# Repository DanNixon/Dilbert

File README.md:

# Dilbert

An interactive badge based on the ESP8266.

For getting started and general information see [GUIDE.md](GUIDE.md).

## Features

- ESP8266
- Colour LCD
- D-pad + A/B buttons
- 8 NeoPixels
- UART, i2c, digital IO and NeoPixel expansion headers

## Links

- Repository: https://github.com/DanNixon/Dilbert
- Travis CI: https://travis-ci.org/DanNixon/Dilbert
- Documentation: http://dannixon.github.io/Dilbert

## Contributing code

Cool stuff to run on the badge is very welcome.

See [CONTRIBUTING.md](CONTRIBUTING.md).

## Requirements

Uses the following Arduino libraries:

- [Adafruit ILI9341](https://github.com/Links2004/Adafruit_ILI9341) (the
  Links2004 fork can provide much faster display updates than the [Adafruit
  library](https://github.com/adafruit/Adafruit_ILI9341))
- [Adafruit GFX](https://github.com/adafruit/Adafruit-GFX-Library)
- [Adafruit NeoPixel](https://github.com/adafruit/Adafruit_NeoPixel)
- [Adafruit MCP23017](https://github.com/adafruit/Adafruit-MCP23017-Arduino-Library)
  (modified version included in this repository)
- [Universal Inputs](https://github.com/DanNixon/ArduinoUniversalInput)

## Parts

- ESP-12
  ([buy](https://www.adafruit.com/product/2491))
- 2.2" TFT display with ILI9341 driver
  ([buy](http://www.ebay.co.uk/itm/262448340175))
- [MCP23017](http://ww1.microchip.com/downloads/en/DeviceDoc/21952b.pdf)
  ([buy](http://www.mouser.co.uk/search/ProductDetail.aspx?R=0virtualkey0virtualkeyMCP23017-E-SO))
- [AP2112](http://www.diodes.com/_files/datasheets/AP2112.pdf)
  ([buy](http://www.digikey.co.uk/product-detail/en/diodes-incorporated/AP2112K-3.3TRG1/AP2112K-3.3TRG1DICT-ND/4505257))
- 8x NeoPixels
  ([buy](https://www.adafruit.com/products/1655))
- 6x switches
  ([buy](http://www.digikey.co.uk/product-detail/en/panasonic-electronic-components/EVQ-PE504K/P13589S-ND/1245482))
- 1uF and 10uF 0805 capacitors
- 1K and 10K 0805 resistors

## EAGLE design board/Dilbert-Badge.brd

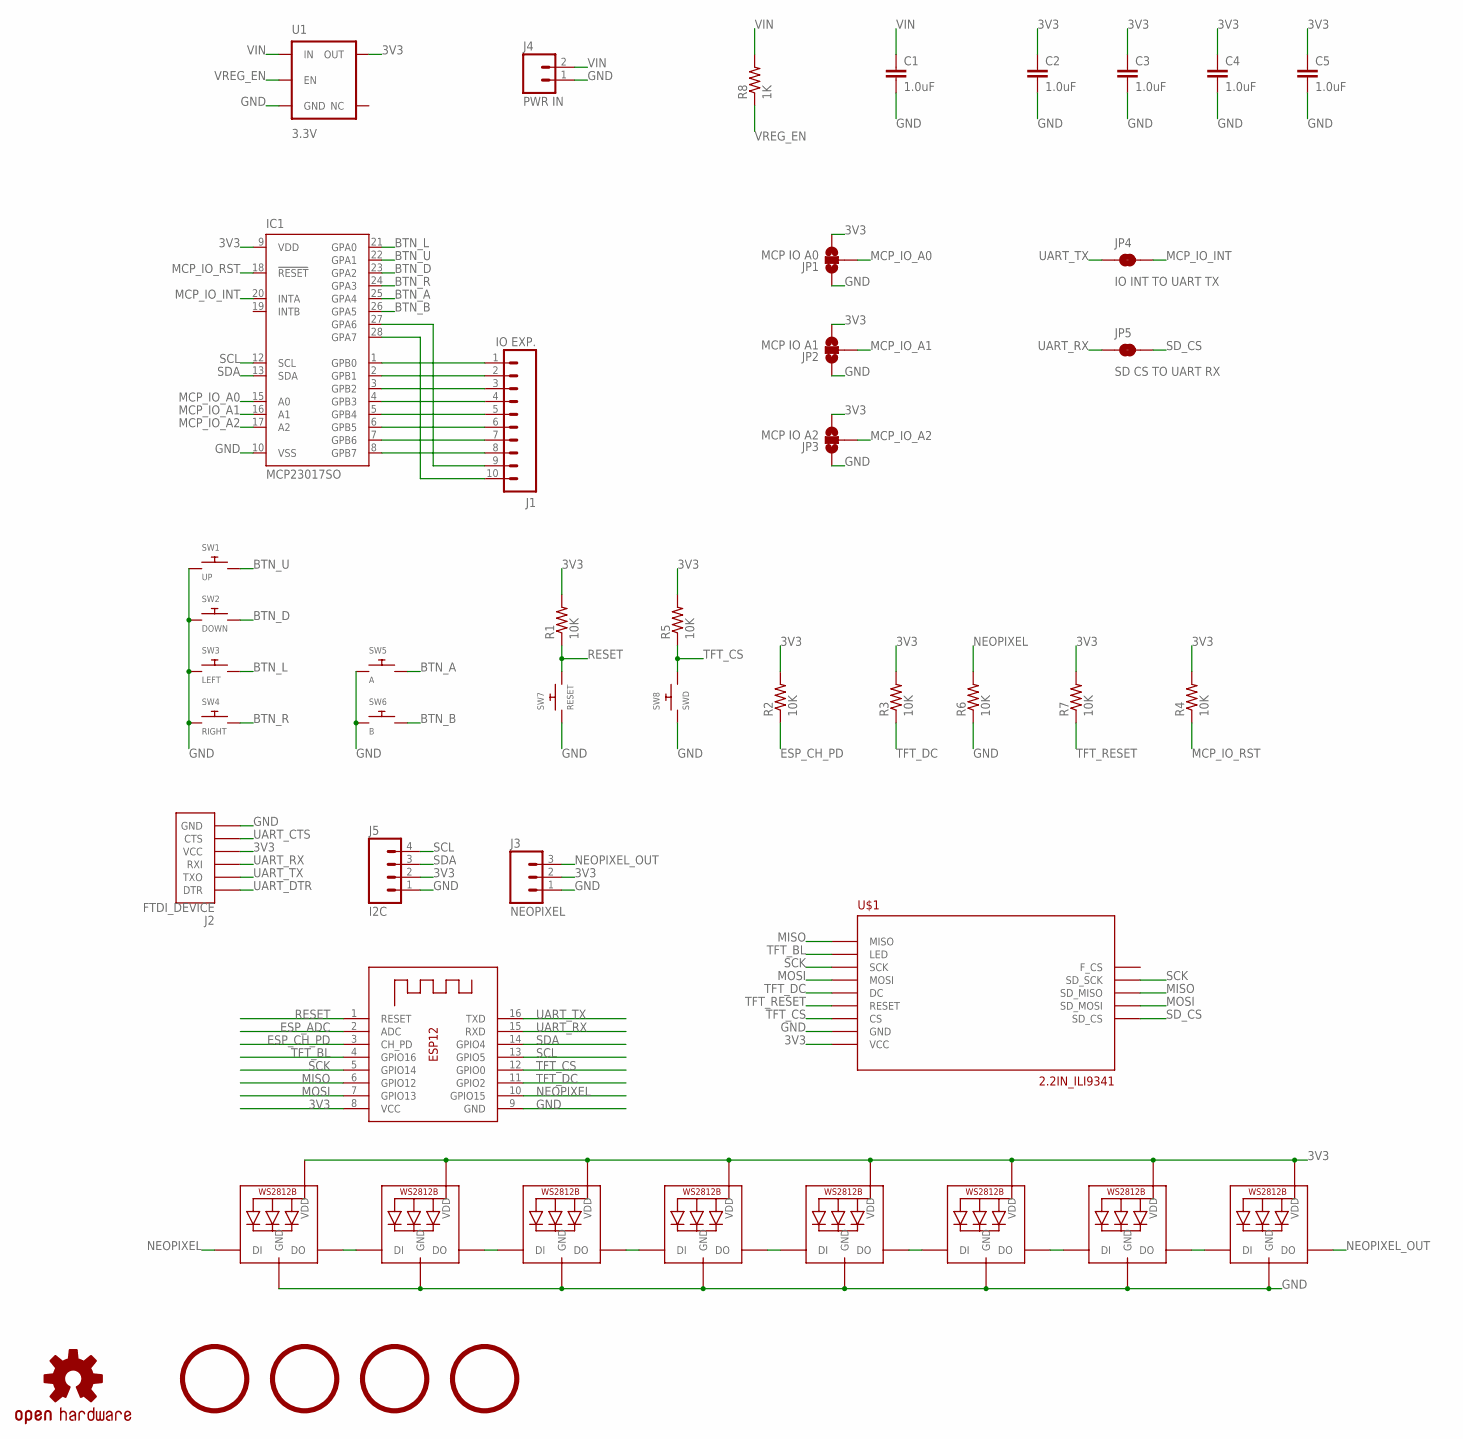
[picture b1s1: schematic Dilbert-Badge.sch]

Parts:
C1, C2, C3, C4, C5: 1.0uF; 0805-CAP
IC1: MCP23017SO; SO28W
J1: IO EXP.; 1X10
J2: FTDI_DEVICE; FTDI_DEVICE_SIDE
J3: NEOPIXEL; 1X03
J4: PWR IN; 1X02
J5: I2C; 1X04
JP1: MCP IO A0; PAD-JUMPER-3-NO_YES_SILK
JP2: MCP IO A1; PAD-JUMPER-3-NO_YES_SILK
JP3: MCP IO A2; PAD-JUMPER-3-NO_YES_SILK
JP4: IO INT TO UART TX; PAD-JUMPER-2-NC_BY_TRACE_NO_SILK
JP5: SD CS TO UART RX; PAD-JUMPER-2-NC_BY_TRACE_NO_SILK
LED1, LED2, LED3, LED4, LED5, LED6, LED7, LED8: WS2812B5050; WS2812B
LOGO1: OSHW-LOGOL; OSHW-LOGO-L
R1, R2, R3, R4, R5, R6, R7: 10K; R0805
R8: 1K; R0805
SW1: UP; TACT_PANA-EVQ
SW2: DOWN; TACT_PANA-EVQ
SW3: LEFT; TACT_PANA-EVQ
SW4: RIGHT; TACT_PANA-EVQ
SW5: A; TACT_PANA-EVQ
SW6: B; TACT_PANA-EVQ
SW7: RESET; TACT_PANA-EVQ
SW8: SWD; TACT_PANA-EVQ
U1: 3.3V; SOT23-5
U$1: 2.2IN_ILI9341
U$2, U$3, U$4, U$5: 5MM_MOUNTING_HOLE; 5MM_HOLE
X1: ESP-12

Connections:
3V3: C2.1, C3.1, C4.1, C5.1, IC1.9 (VDD), J2.P$4 (VCC), J3.2, J5.2, JP1.3, JP2.3, JP3.3, LED1.1-VDD (VDD), LED2.1-VDD (VDD), LED3.1-VDD (VDD), LED4.1-VDD (VDD), LED5.1-VDD (VDD), LED6.1-VDD (VDD), LED7.1-VDD (VDD), LED8.1-VDD (VDD), R1.2, R2.2, R3.2, R4.2, R5.2, R7.2, U1.5 (OUT), U$1.VCC, X1.8 (VCC)
BTN_A: IC1.25 (GPA4), SW5.P$2
BTN_B: IC1.26 (GPA5), SW6.P$2
BTN_D: IC1.23 (GPA2), SW2.P$2
BTN_L: IC1.21 (GPA0), SW3.P$2
BTN_R: IC1.24 (GPA3), SW4.P$2
BTN_U: IC1.22 (GPA1), SW1.P$2
ESP_ADC: X1.2 (ADC)
ESP_CH_PD: R2.1, X1.3 (CH_PD)
GND: C1.2, C2.2, C3.2, C4.2, C5.2, IC1.10 (VSS), J2.P$6 (GND), J3.1, J4.1, J5.1, JP1.1, JP2.1, JP3.1, LED1.3-GND (GND), LED2.3-GND (GND), LED3.3-GND (GND), LED4.3-GND (GND), LED5.3-GND (GND), LED6.3-GND (GND), LED7.3-GND (GND), LED8.3-GND (GND), R6.1, SW1.P$1, SW2.P$1, SW3.P$1, SW4.P$1, SW5.P$1, SW6.P$1, SW7.P$1, SW8.P$1, U1.2 (GND), U$1.GND, X1.9 (GND)
MCP_IO_A0: IC1.15 (A0), JP1.2
MCP_IO_A1: IC1.16 (A1), JP2.2
MCP_IO_A2: IC1.17 (A2), JP3.2
MCP_IO_INT: IC1.20 (INTA), JP4.2
MCP_IO_RST: IC1.18 (!RESET), R4.1
MISO: U$1.MISO, U$1.SD_MISO, X1.6 (GPIO12)
MOSI: U$1.MOSI, U$1.SD_MOSI, X1.7 (GPIO13)
unnamed: LED1.2-DOUT (DO), LED2.4-DIN (DI)
unnamed: IC1.1 (GPB0), J1.1
unnamed: IC1.2 (GPB1), J1.2
unnamed: IC1.3 (GPB2), J1.3
unnamed: IC1.4 (GPB3), J1.4
unnamed: IC1.28 (GPA7), J1.10
unnamed: IC1.27 (GPA6), J1.9
unnamed: IC1.8 (GPB7), J1.8
unnamed: IC1.7 (GPB6), J1.7
unnamed: IC1.6 (GPB5), J1.6
unnamed: IC1.5 (GPB4), J1.5
unnamed: LED2.2-DOUT (DO), LED3.4-DIN (DI)
unnamed: LED3.2-DOUT (DO), LED4.4-DIN (DI)
unnamed: LED4.2-DOUT (DO), LED5.4-DIN (DI)
unnamed: LED5.2-DOUT (DO), LED6.4-DIN (DI)
unnamed: LED6.2-DOUT (DO), LED7.4-DIN (DI)
unnamed: LED7.2-DOUT (DO), LED8.4-DIN (DI)
NEOPIXEL: LED1.4-DIN (DI), R6.2, X1.10 (GPIO15)
NEOPIXEL_OUT: J3.3, LED8.2-DOUT (DO)
RESET: R1.1, SW7.P$2, X1.1 (RESET)
SCK: U$1.SCK, U$1.SD_SCK, X1.5 (GPIO14)
SCL: IC1.12 (SCL), J5.4, X1.13 (GPIO5)
SDA: IC1.13 (SDA), J5.3, X1.14 (GPIO4)
SD_CS: JP5.2, U$1.SD_CS
TFT_BL: U$1.LED, X1.4 (GPIO16)
TFT_CS: R5.1, SW8.P$2, U$1.CS, X1.12 (GPIO0)
TFT_DC: R3.1, U$1.DC, X1.11 (GPIO2)
TFT_RESET: R7.1, U$1.RESET
UART_CTS: J2.P$5 (CTS)
UART_DTR: J2.P$1 (DTR)
UART_RX: J2.P$3 (RXI), JP5.1, X1.15 (RXD)
UART_TX: J2.P$2 (TXO), JP4.1, X1.16 (TXD)
VIN: C1.1, J4.2, R8.2, U1.1 (IN)
VREG_EN: R8.1, U1.3 (EN)

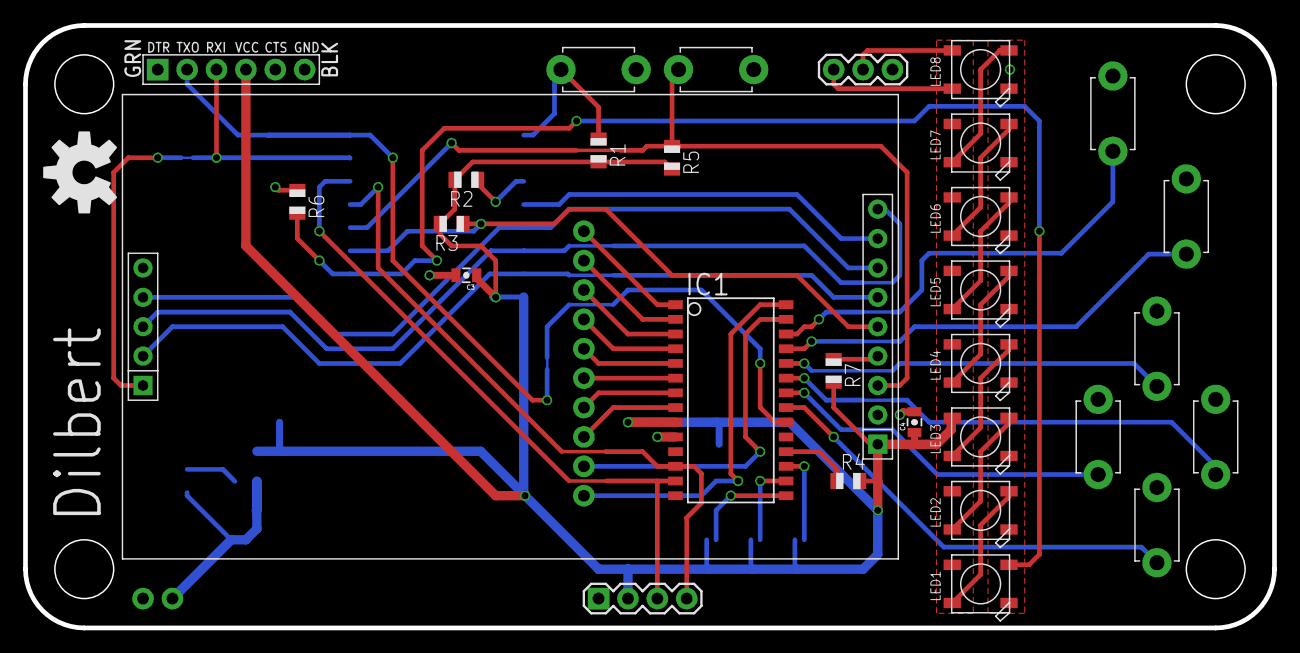
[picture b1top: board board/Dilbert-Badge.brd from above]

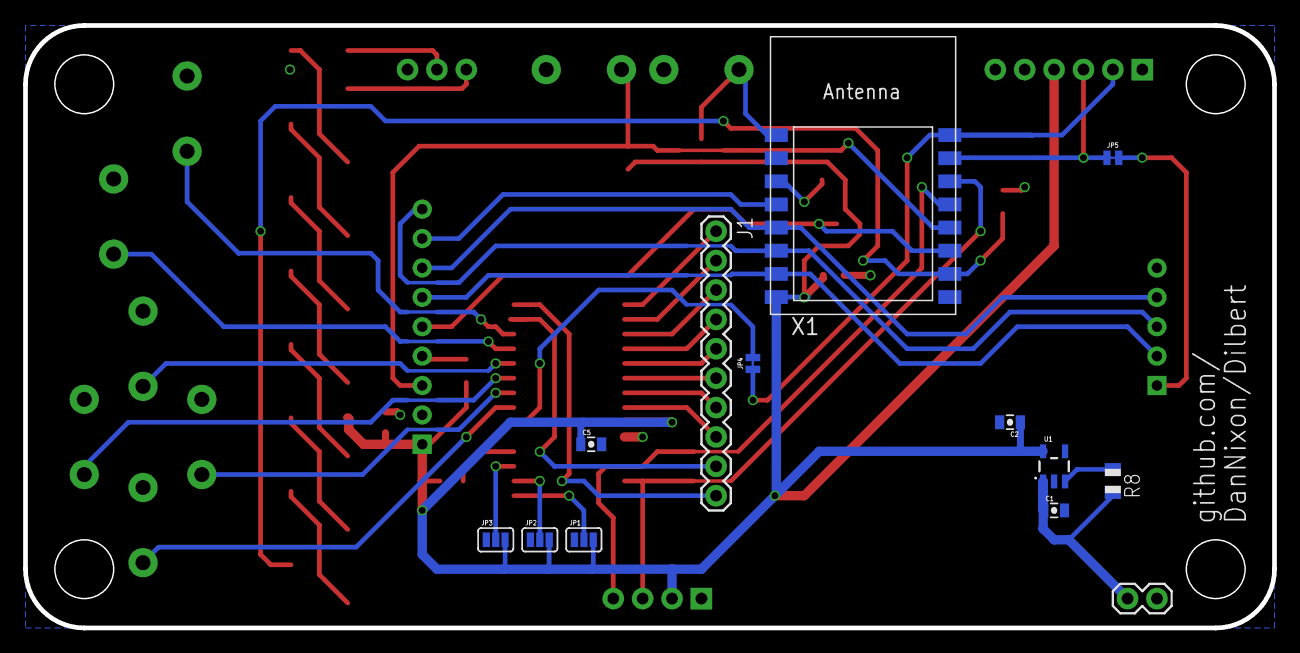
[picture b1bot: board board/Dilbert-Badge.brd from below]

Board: 2 copper layers, 108.0 x 52.1 mm, 48 parts (13 on the bottom side), 48 nets.

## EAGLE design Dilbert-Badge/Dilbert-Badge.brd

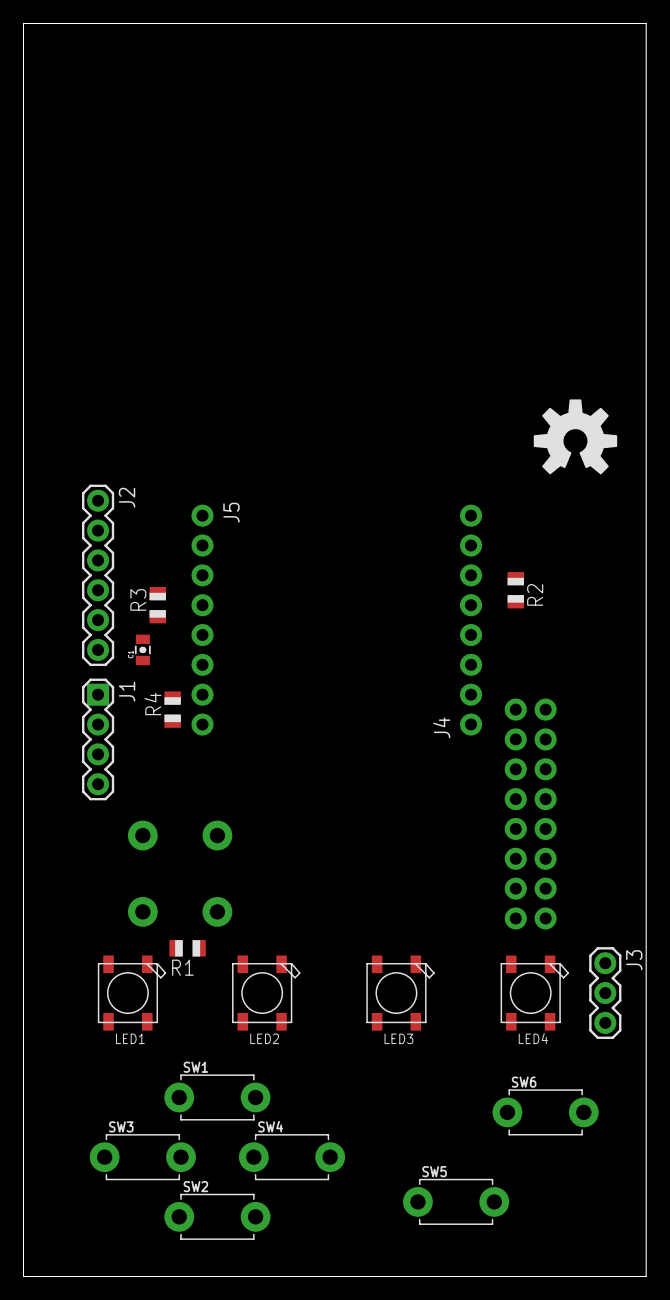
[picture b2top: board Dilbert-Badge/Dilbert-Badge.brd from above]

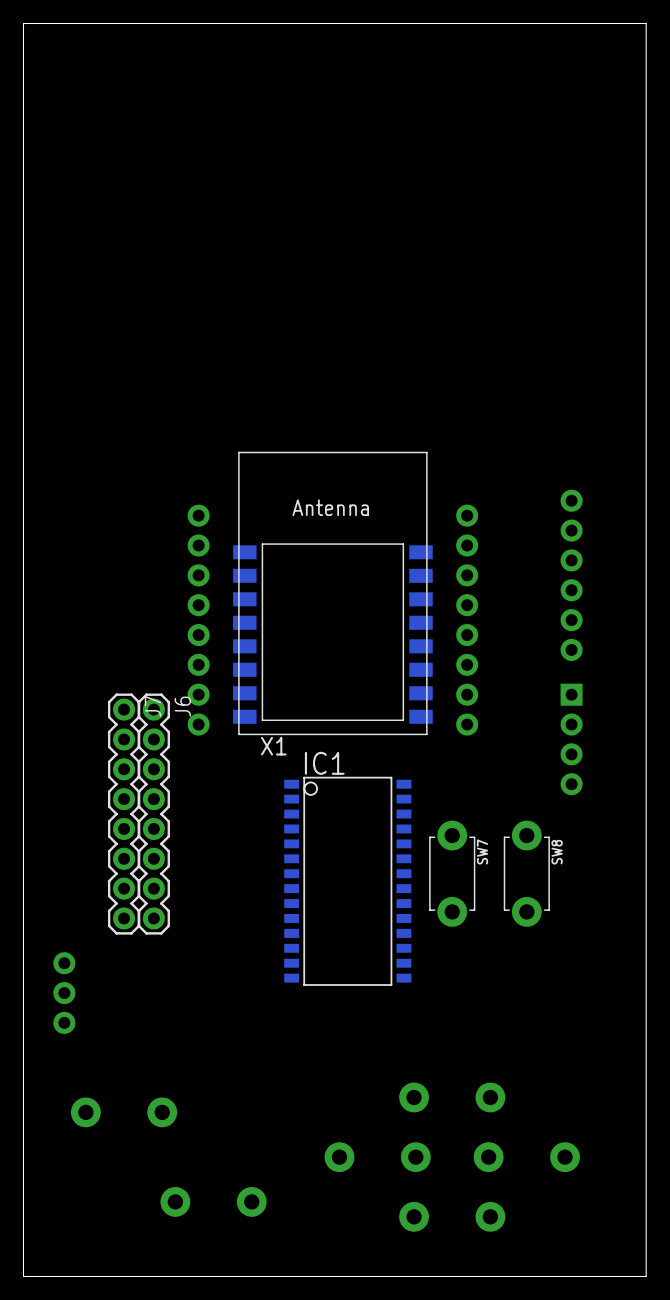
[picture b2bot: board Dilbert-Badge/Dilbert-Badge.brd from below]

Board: 2 copper layers, 53.0 x 106.7 mm, 27 parts (6 on the bottom side), 36 nets, no tracks yet.

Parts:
C1: 0805-CAP
IC1: MCP23017SO; SO28W
J1: I2C; 1X04
J2: UART; 1X06
J3: 1X03
J4, J5: 1X08_NO_SILK
J6: IO_B; 1X08_ROUND
J7: IO_A; 1X08_ROUND
LED1, LED2, LED3, LED4: WS2812B5050; WS2812B
LOGO1: OSHW-LOGOL; OSHW-LOGO-L
R1, R2, R3: 10K; R0805
R4: R0805
SW1: UP; TACT_PANA-EVQ
SW2: DOWN; TACT_PANA-EVQ
SW3: LEFT; TACT_PANA-EVQ
SW4: RIGHT; TACT_PANA-EVQ
SW5: A; TACT_PANA-EVQ
SW6: B; TACT_PANA-EVQ
SW7: RESET; TACT_PANA-EVQ
SW8: SWD; TACT_PANA-EVQ
X1: ESP-12

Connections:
3V3: C1.1, IC1.9, J1.2, J2.4, J3.2, J4.1, LED1.1-VDD, LED2.1-VDD, LED3.1-VDD, LED4.1-VDD, R1.2, R2.2, R3.2, X1.8
BTN_A: IC1.25, J7.5, SW5.P$2
BTN_B: IC1.26, J7.6, SW6.P$2
BTN_D: IC1.22, J7.2, SW2.P$2
BTN_L: IC1.23, J7.3, SW3.P$2
BTN_R: IC1.24, J7.4, SW4.P$2
BTN_U: IC1.21, J7.1, SW1.P$2
ESP_ADC: J4.7, X1.2
ESP_CH_PD: J4.6, R2.1, X1.3
GND: C1.2, IC1.10, J1.1, J2.6, J3.1, J5.8, LED1.3-GND, LED2.3-GND, LED3.3-GND, LED4.3-GND, R4.1, SW1.P$1, SW2.P$1, SW3.P$1, SW4.P$1, SW5.P$1, SW6.P$1, SW7.P$1, SW8.P$1, X1.9
GPIO2: J5.6, R3.1, X1.11
LED_IN: J5.7, LED1.4-DIN, R4.2, X1.10
LED_OUT: J3.3, LED4.2-DOUT
unnamed: LED1.2-DOUT, LED2.4-DIN
unnamed: LED2.2-DOUT, LED3.4-DIN
unnamed: LED3.2-DOUT, LED4.4-DIN
unnamed: J4.5, X1.4
unnamed: J4.4, X1.5
unnamed: J4.2, X1.7
unnamed: J4.3, X1.6
unnamed: J5.3, X1.14
unnamed: IC1.1, J6.1
unnamed: IC1.2, J6.2
unnamed: IC1.8, J6.8
unnamed: IC1.7, J6.7
unnamed: IC1.6, J6.6
unnamed: IC1.5, J6.5
unnamed: IC1.4, J6.4
unnamed: IC1.3, J6.3
unnamed: IC1.28, J7.8
unnamed: IC1.27, J7.7
RESET: J4.8, R1.1, SW7.P$2, X1.1
SCL: IC1.12, J1.4, J5.5, SW8.P$2, X1.12
SDA: IC1.13, J1.3, J5.4, X1.13
UART_RX: J2.3, J5.2, X1.15
UART_TX: J2.2, J5.1, X1.16

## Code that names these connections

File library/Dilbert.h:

/*! @file */

#ifndef _DILBERT_H_
#define _DILBERT_H_

#include <Adafruit_NeoPixel.h>
#include <Adafruit_ILI9341.h>
#include <UniversalInputManager.h>

#include "Adafruit_MCP23017.h"

/**
 * @class Dilbert
 * @author Dan Nixon
 * @brief Main hardware abstraction class.
 */
class Dilbert
{
public:
  static const uint8_t MCP23017_INT_GPIO = 1;   //!< MCP23017 interrupt GPIO (on UART0 Tx)
  static const uint8_t SD_CS_GPIO = 3;          //!< SD chip select GPIO (on UART0 Rx)
  static const uint8_t TFT_CS_GPIO = 0;         //!< TFT chip select GPIO
  static const uint8_t TFT_DC_GPIO = 2;         //!< TFT DC GPIO
  static const uint8_t TFT_BACKLIGHT_GPIO = 16; //!< TFT backlight GPIO
  static const uint8_t NEOPIXEL_GPIO = 15;      //!< NeoPIxel GPIO

  static const uint8_t BUTTON_UP = 1;    //!< Up buppion GPIO (on MCP23017)
  static const uint8_t BUTTON_DOWN = 2;  //!< Down button GPIO (on MCP23017)
  static const uint8_t BUTTON_LEFT = 0;  //!< Left button GPIO (on MCP23017)
  static const uint8_t BUTTON_RIGHT = 3; //!< Right button GPIO (on MCP23017)
  static const uint8_t BUTTON_A = 4;     //!< A button GPIO (on MCP23017)
  static const uint8_t BUTTON_B = 5;     //!< B button GPIO (on MCP23017)

public:
  Dilbert();
  virtual ~Dilbert();

  void begin(size_t numNeoPixels = 8);

  /**
   * @brief Gets the TFT display driver.
   * @returns Reference to display driver
   */
  inline Adafruit_ILI9341 &display()
  {
    return *m_tftDisplay;
  }

  /**
   * @brief Gets the backlight intensity.
   * @return Intensity
   *
   * Where 0 is off and 1023 is brightest.
   */
  uint16_t backlight() const
  {
    return m_backlightIntensity;
  }

  void setBacklightOn(bool on);
  void setBacklight(uint16_t intensity);

  /**
   * @brief Gets the NeoPixel LED driver.
   * @return Reference to NeoPixel driver
   */
  inline Adafruit_NeoPixel &neoPixels()
  {
    return *m_neopixels;
  }

  /**
   * @brief Gets the IO expender driver.
   * @return Reference to the IO expander driver
   *
   * Warning: some of the IO pins are used for specific functions that are
   * managed elsewhere, do not set a pin that alreadyhas a function, this will
   * probably break something else.
   */
  inline Adafruit_MCP23017 &io()
  {
    return *m_io;
  }

  /**
   * @brief Gets the button manager.
   * @return Reference to the button manager
   */
  inline UniversalInputManager &buttons()
  {
    return *m_buttons;
  }

private:
  Adafruit_MCP23017 *m_io; //!< IO expander driver

  Adafruit_ILI9341 *m_tftDisplay; //<! Display driver
  uint16_t m_backlightIntensity;  //!< Backlight intensity (0-1023)

  UniversalInputManager *m_buttons; //!< Button manager

  Adafruit_NeoPixel *m_neopixels; //!< NeoPixel driver
};

#endif

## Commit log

2016-05-19 initial docs
2016-05-19 feature creep has begun
2016-05-20 start board
2016-05-20 add switches, initial layout
2016-05-20 a little more work
2016-05-20 update docs
2016-05-20 add IO expander, more general layout
2016-05-22 add puller resistors and decouping
2016-05-27 add initial library
2016-05-27 add parts list
2016-05-27 add display test
2016-05-27 update exaple and fix CI issue
2016-05-27 use generic pins
2016-05-27 add neopixels
2016-05-27 rename demo
2016-05-27 clang-format
2016-05-27 no TFT debug
    [ci skip]
2016-05-27 Update board
    [ci skip]
2016-05-27 Remove CI for now
    Seems like it does not want to work so just remove for now
2016-05-27 add format code script
2016-05-27 add libs
2016-05-27 add ability to use MC IO expander for TFT
2016-05-27 More dev work
2016-06-01 more work on board
2016-06-04 more work
2016-06-04 more neopixels are good
2016-06-07 switch to hardware SPI with i2c port expander
2016-06-08 get working again with interrups for port expander
    Curently HardwareDemo shows the port status of the MCP when the state of
    any pin changes, the backlight gets brighter to indicate the interrupt
    being fired.
2016-06-08 swap pins
2016-06-09 board updates
2016-06-09 more board layout
2016-06-09 more layout
2016-06-09 correct switches, more layout
2016-06-09 ERC/DRU checks
2016-06-09 add regulator, tidy layout
2016-06-10 clean up text, maximise gropund plane width
2016-06-10 add hole for landscape lanyard
2016-06-10 add images
2016-06-10 swap left/right buttons
2016-06-10 Moved layout for better hold position.
2016-06-10 Revert "Moved layout for better hold position."
    This reverts commit 4734362e310bc9f544577fd27d433fa3af5f158a.
2016-06-10 Redo Alistair's new layout
2016-06-10 update DRC
2016-06-11 update lcd pads and routing
2016-06-11 add button manager
2016-06-12 docs
2016-06-12 add buttons
2016-06-24 testing
2016-06-24 WIder power planes on NeoPixels
    Fixes #4
2016-06-24 Remove images
    (just install Eagle, it's not difficult)
2016-06-29 get buttons working
2016-06-29 small updates
2016-06-29 option of interrupts in demo
2016-06-29 add a basic setup guide
2016-06-29 update docs and guide
2016-06-29 more power notes
2016-06-30 add manager skeleton
2016-07-01 refactoring, add app manager code
2016-07-01 basic app examples
2016-07-01 add app switching example
2016-07-01 app manager fully working
2016-07-01 add profile app
2016-07-01 rename
2016-07-01 more updates
2016-07-01 start adding docs
2016-07-01 build docs
2016-07-01 doxygen config updates
2016-07-01 include all files in docs
2016-07-01 more docs
2016-07-01 Set background colour in App
    Fixes #5
2016-07-01 fix doxygen
2016-07-02 docs and clang-forat to 100 cols
2016-07-03 more demo apps, smaller text, fix memory issue
2016-07-09 small updates to board
2016-07-29 Update Doxyfile
2016-07-30 Too many demos
2016-08-02 Initial files for settings manager
    [ci skip]
2016-08-02 Fix build
    [ci skip]
2016-08-02 Initial working version of config manager and backlight control
2016-08-02 DO not require B to be released to exit an app
2016-08-02 Set backlight on by default
2016-08-02 Fix docs
2016-08-03 delay before backlight on
2016-08-03 Officially recommend the Links2004 fork of TFT driver
    Closes #8
2016-08-03 feed the backlight when an app is quit using B
2016-08-03 initial settings app
    shows values
2016-08-03 Prevent backlight timeout with value of 0 in timeout
2016-08-03 Revert "Added Stars"
2016-08-03 Added Stars App
2016-08-04 Minor refactoring
2016-08-04 clang format
2016-08-04 Dilbert ASCII Art app added
2016-08-04 add build back into travis ci
2016-08-04 Add missing libs
2016-08-04 use https in clone
2016-08-04 Fix GFX clone
2016-08-04 fix a typo
2016-08-04 Fix path
2016-08-04 fix includes
2016-08-04 Bug fix and multiple star sizes
    Bug fixed for stars created in centre.
    multiple star sizes added.
2016-08-05 Fix more includes, because Arduino
2016-08-05 Small tweeks
2016-08-05 Stars App Fixes and Multiple Star Sizes re-applied
2016-08-05 added kewly shit like conways do I need to say any more?
2016-08-05 add missing files
2016-08-05 leh fails imma rektiffy o_0
2016-08-05 Fix ctors
2016-08-05 clang-format
    fixin' jon's code
2016-08-06 SYstem config app done, reworked config
2016-08-06 remove extra file
2016-08-06 sensible default values
2016-08-06 skeleton files
2016-08-06 add pers storage
2016-08-06 more backlight control
2016-08-06 doc all files, add backlight timeout to profile app
2016-08-07 formatting and docs
2016-08-07 backlight stuff
2016-08-09 Initial switch to platformio build
2016-08-09 fix travis.yml
2016-08-09 more refactoring
2016-08-09 CI updates
2016-08-09 small fix
2016-08-09 Refactor neopixel app
    CLoses #14
2016-08-13 standards
    [ci skip]
2016-08-13 fix issue with neotestapp
2016-08-14 small couple of fixes
2016-08-14 remove old test projects
2016-08-14 add extra step
    [ci skip]
2016-08-14 manual deploy
2016-08-14 clean
2016-08-14 add macros to profile app for different profiles
2016-08-14 several app updates, add wifi, start weather app
2016-08-15 more updates, new debug app, use JSON for config
2016-08-20 add debug app
2016-08-20 Add Jon's profile
2016-09-01 Added a subset of the Adafruit GFX library
    Fix for sysetms that do not have the freetype font library installed.
    Fontconvert is not used but platformio tries to compile it anyway.
2017-03-27 use #pragma once
2017-03-27 add skeleton app

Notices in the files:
parts and their libraries:
SparkFun-Connectors: Licensing: Creative Commons ShareAlike 4.0 International - https://creativecommons.org/licenses/by-sa/4.0
